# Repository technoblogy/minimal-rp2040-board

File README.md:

# Minimal RP2040 Board
Eagle files for a minimal breakout board based on the Raspberry Pi RP2040 processor.

See <http://www.technoblogy.com/show?3U75>.

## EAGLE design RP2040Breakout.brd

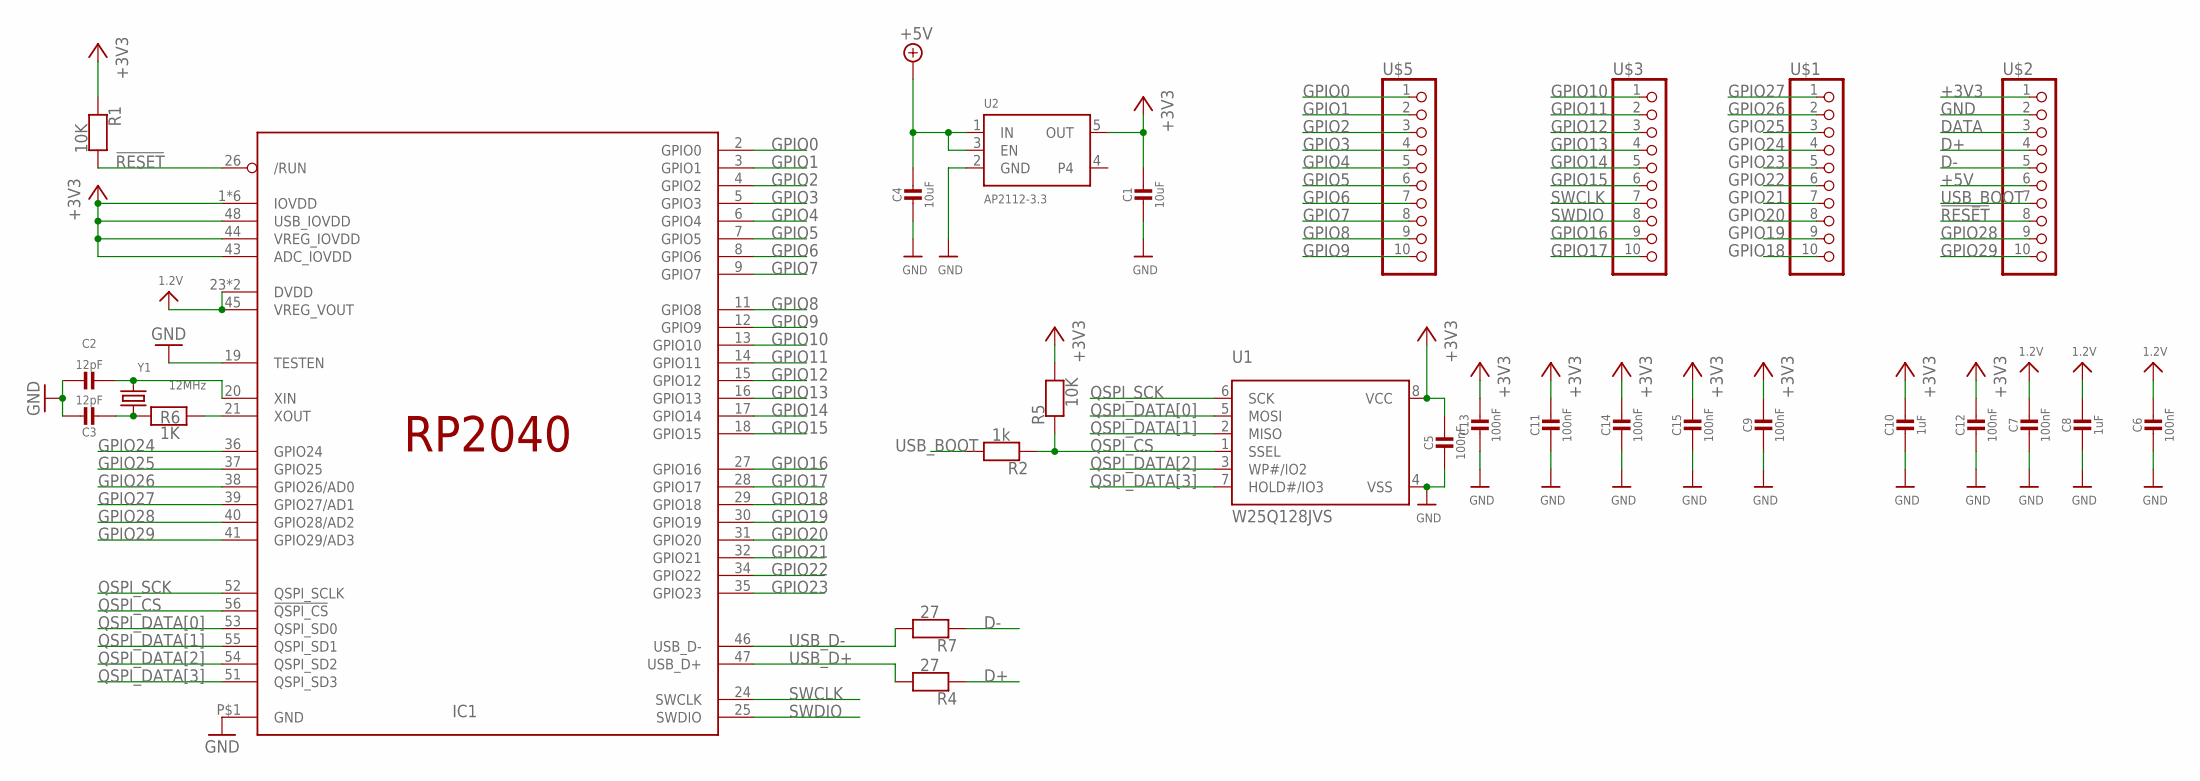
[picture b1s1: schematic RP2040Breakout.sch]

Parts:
C1, C4: 10uF; _0805MP
C2, C3: 12pF; _0402NO
C5, C6, C7, C9, C11, C12, C13, C14, C15: 100nF; _0402NO
C8, C10: 1uF; _0402NO
IC1: RP2040_QFN56; QFN56_7MM_REDUCEDEPAD
R1, R5: 10K; _0402NO
R2: 1k; _0402NO
R4, R7: 27; _0402NO
R6: 1K; _0402NO
U1: W25Q128JVS; SOIC8_208MIL
U2: AP2112-3.3; SOT23-5@1
U$1, U$2, U$3, U$5: HEADER-1X10ROUND; 1X10_ROUND
Y1: 12MHz; CRYSTAL-SMD-5X3

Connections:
1.2V: C6.1, C7.1, C8.1, IC1.23 (DVDD), IC1.45 (VREG_VOUT), IC1.50 (DVDD)
!RESET: IC1.26 (/RUN), R1.2, U$2.8
+3V3: C1.1, C5.1, C9.1, C10.1, C11.1, C12.1, C13.1, C14.1, C15.1, IC1.1 (IOVDD), IC1.10 (IOVDD), IC1.22 (IOVDD), IC1.33 (IOVDD), IC1.42 (IOVDD), IC1.43 (ADC_IOVDD), IC1.44 (VREG_IOVDD), IC1.48 (USB_IOVDD), IC1.49 (IOVDD), R1.1, R5.2, U1.8 (VCC), U2.5 (OUT), U$2.1
+5V: C4.1, U2.1 (IN), U2.3 (EN), U$2.6
D+: R4.1, U$2.4
D-: R7.1, U$2.5
DATA: U$2.3
GND: C1.2, C2.1, C3.1, C4.2, C5.2, C6.2, C7.2, C8.2, C9.2, C10.2, C11.2, C12.2, C13.2, C14.2, C15.2, IC1.19 (TESTEN), IC1.P$1 (GND), U1.4 (VSS), U2.2 (GND), U$2.2
GPIO0: IC1.2 (GPIO0), U$5.1
GPIO1: IC1.3 (GPIO1), U$5.2
GPIO2: IC1.4 (GPIO2), U$5.3
GPIO3: IC1.5 (GPIO3), U$5.4
GPIO4: IC1.6 (GPIO4), U$5.5
GPIO5: IC1.7 (GPIO5), U$5.6
GPIO6: IC1.8 (GPIO6), U$5.7
GPIO7: IC1.9 (GPIO7), U$5.8
GPIO8: IC1.11 (GPIO8), U$5.9
GPIO9: IC1.12 (GPIO9), U$5.10
GPIO10: IC1.13 (GPIO10), U$3.1
GPIO11: IC1.14 (GPIO11), U$3.2
GPIO12: IC1.15 (GPIO12), U$3.3
GPIO13: IC1.16 (GPIO13), U$3.4
GPIO14: IC1.17 (GPIO14), U$3.5
GPIO15: IC1.18 (GPIO15), U$3.6
GPIO16: IC1.27 (GPIO16), U$3.9
GPIO17: IC1.28 (GPIO17), U$3.10
GPIO18: IC1.29 (GPIO18), U$1.10
GPIO19: IC1.30 (GPIO19), U$1.9
GPIO20: IC1.31 (GPIO20), U$1.8
GPIO21: IC1.32 (GPIO21), U$1.7
GPIO22: IC1.34 (GPIO22), U$1.6
GPIO23: IC1.35 (GPIO23), U$1.5
GPIO24: IC1.36 (GPIO24), U$1.4
GPIO25: IC1.37 (GPIO25), U$1.3
GPIO26: IC1.38 (GPIO26/AD0), U$1.2
GPIO27: IC1.39 (GPIO27/AD1), U$1.1
GPIO28: IC1.40 (GPIO28/AD2), U$2.9
GPIO29: IC1.41 (GPIO29/AD3), U$2.10
unnamed: IC1.21 (XOUT), R6.2
unnamed: C2.2, IC1.20 (XIN), Y1.3 (2)
unnamed: C3.2, R6.1, Y1.1
QSPI_CS: IC1.56 (!QSPI_CS), R2.1, R5.1, U1.1 (SSEL)
QSPI_DATA[0]: IC1.53 (QSPI_SD0), U1.5 (MOSI)
QSPI_DATA[1]: IC1.55 (QSPI_SD1), U1.2 (MISO)
QSPI_DATA[2]: IC1.54 (QSPI_SD2), U1.3 (WP#/IO2)
QSPI_DATA[3]: IC1.51 (QSPI_SD3), U1.7 (HOLD#/IO3)
QSPI_SCK: IC1.52 (QSPI_SCLK), U1.6 (SCK)
SWCLK: IC1.24 (SWCLK), U$3.7
SWDIO: IC1.25 (SWDIO), U$3.8
USB_BOOT: R2.2, U$2.7
USB_D+: IC1.47 (USB_D+), R4.2
USB_D-: IC1.46 (USB_D-), R7.2

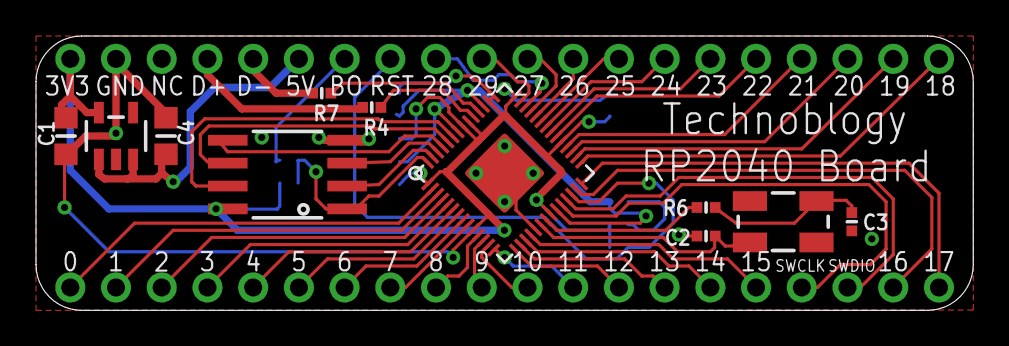
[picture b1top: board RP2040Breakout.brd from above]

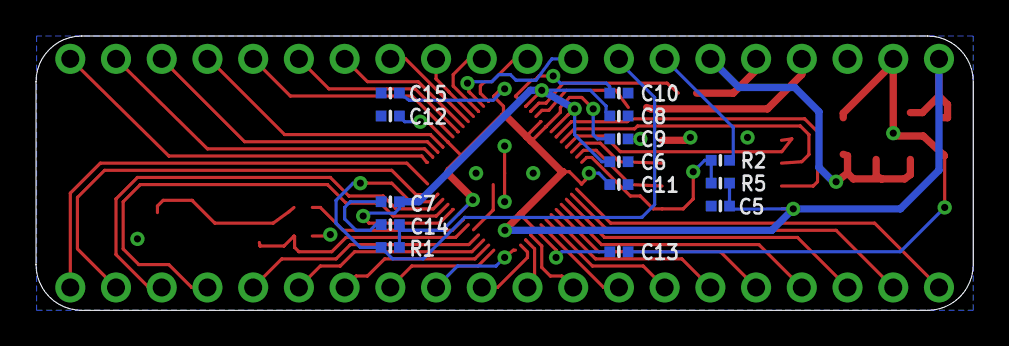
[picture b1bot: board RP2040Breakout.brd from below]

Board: 2 copper layers, 52.1 x 15.2 mm, 29 parts (14 on the bottom side), 51 nets.

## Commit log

2022-04-12 Version 1: 12th April 2022
2023-08-11 License

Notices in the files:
parts and their libraries:
microbuilder: This work is placed in the public domain, and may be freely used for commercial and non-commercial work with the following conditions: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
SparkFun-FreqCtrl: Licensing: Creative Commons ShareAlike 4.0 International - https://creativecommons.org/licenses/by-sa/4.0
